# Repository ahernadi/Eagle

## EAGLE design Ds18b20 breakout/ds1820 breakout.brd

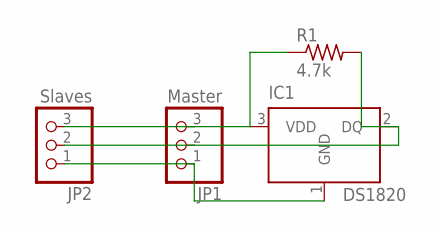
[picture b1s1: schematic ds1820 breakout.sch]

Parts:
IC1: DS1820; TO-92
JP1: Master; 1X03
JP2: Slaves; 1X03
R1: 4.7k; 0207/7

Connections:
GND: IC1.1 (GND), JP1.1, JP2.1
unnamed: IC1.2 (DQ), JP1.2, JP2.2, R1.2
VCC: IC1.3 (VDD), JP1.3, JP2.3, R1.1

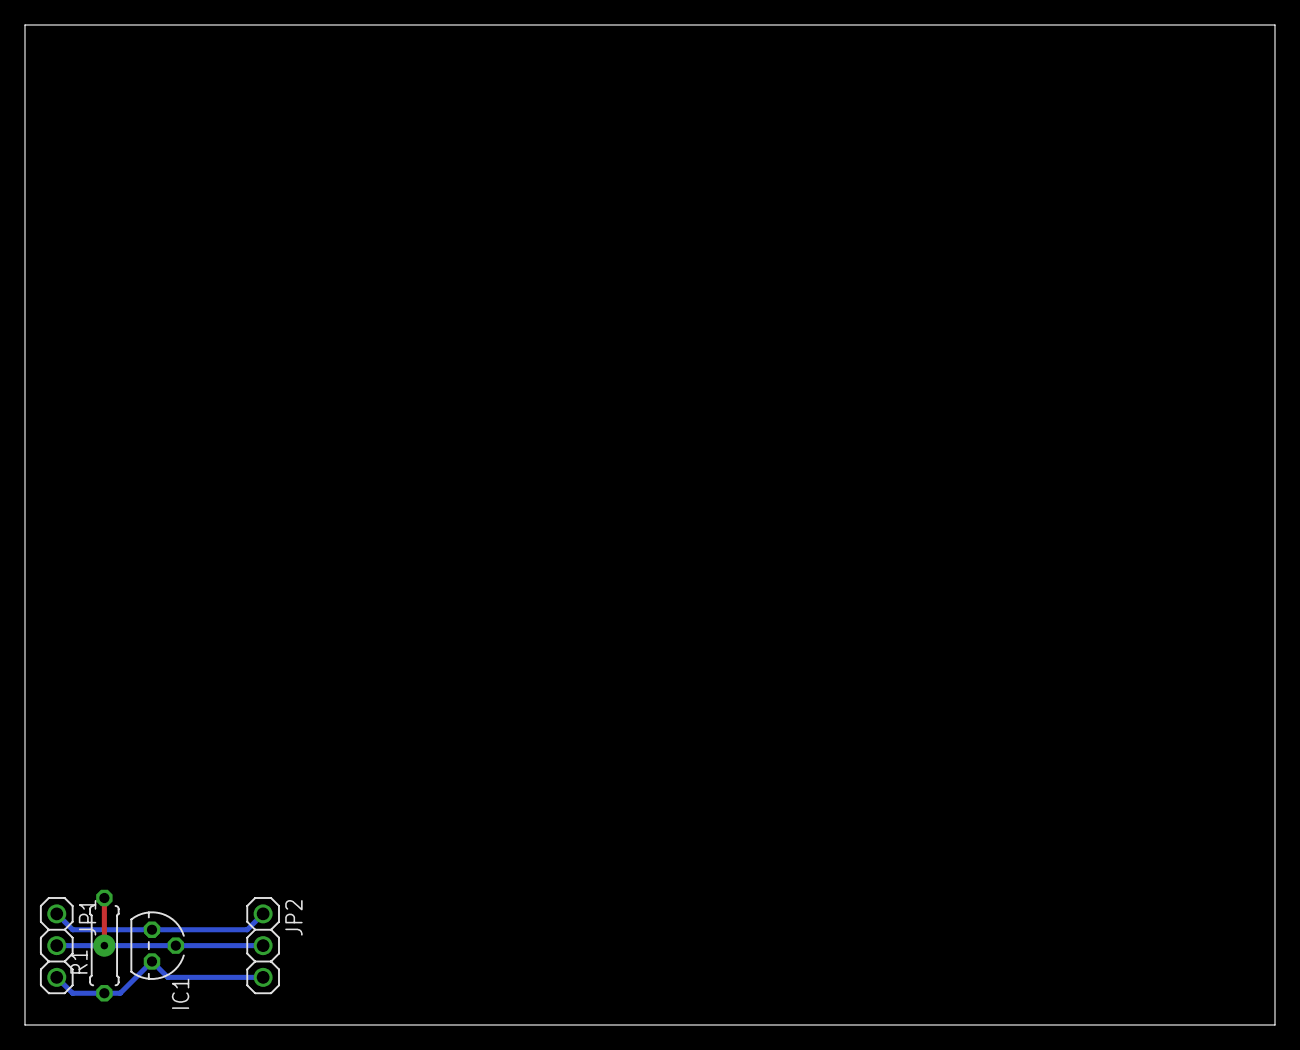
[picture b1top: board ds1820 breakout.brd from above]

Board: 2 copper layers, 100.0 x 80.0 mm, 4 parts (0 on the bottom side), 3 nets.

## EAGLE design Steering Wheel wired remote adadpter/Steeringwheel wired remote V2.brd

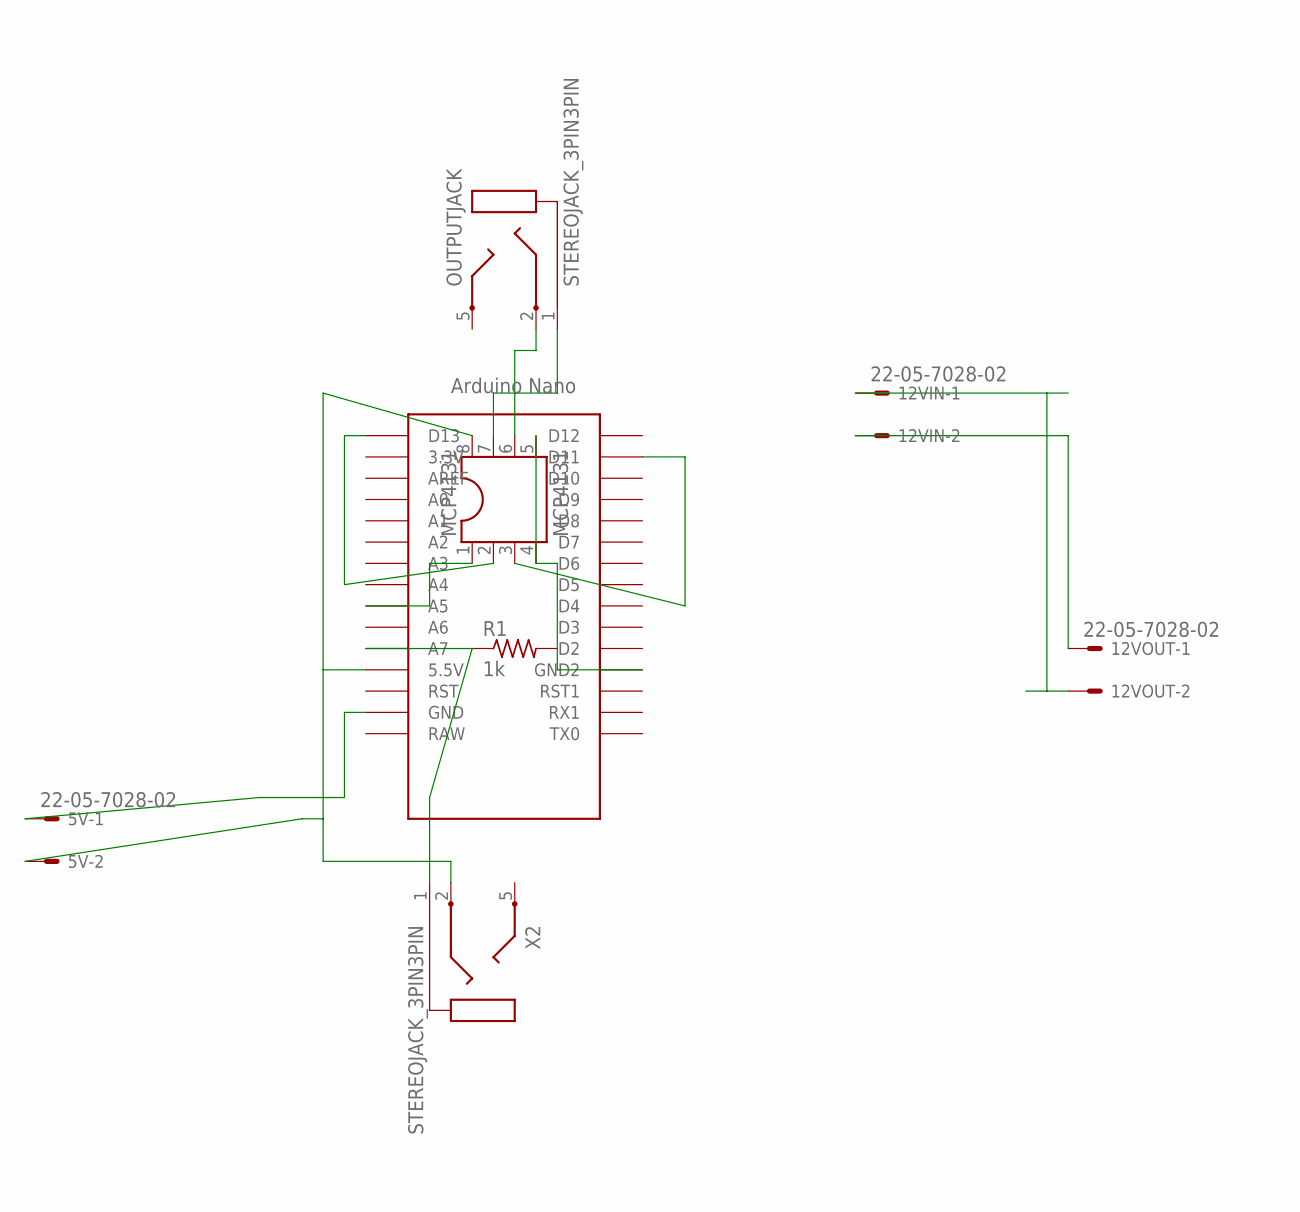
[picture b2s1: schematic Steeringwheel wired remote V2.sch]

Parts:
5V, 12VIN, 12VOUT: 22-05-7028-02; 7395-02
IC1: MCP4131; DIL08
OUTPUTJACK: STEREOJACK_3PIN3PIN; STX3000
R1: 1k; 0204/5
U$2: NANO; NANO_NOISPC
X2: STEREOJACK_3PIN3PIN; STX3000

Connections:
GND: 5V.1, IC1.4 (GND), IC1.5 (P0A), R1.2, U$2.GND, U$2.GND1 (GND2)
unnamed: IC1.3 (SDI), U$2.D11
unnamed: IC1.2 (SCK), U$2.D13
unnamed: R1.1, U$2.A7, X2.1
unnamed: IC1.6 (P0W), OUTPUTJACK.2
unnamed: 5V.2, IC1.8 (VCC), U$2.5V (5.5V), X2.2
unnamed: 12VIN.1, 12VOUT.2
unnamed: 12VIN.2, 12VOUT.1
unnamed: IC1.1 (!CS), U$2.A5
unnamed: IC1.7 (P0B), OUTPUTJACK.1

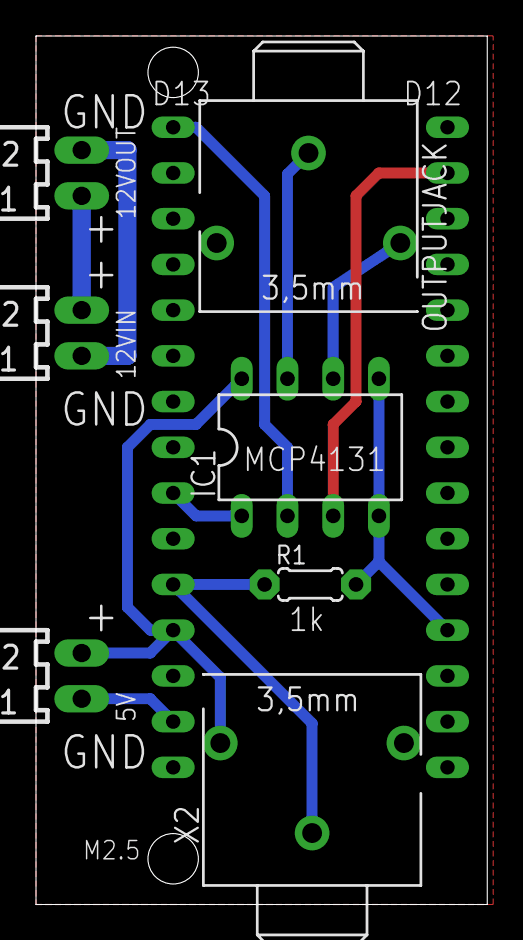
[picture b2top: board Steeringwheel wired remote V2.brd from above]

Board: 2 copper layers, 25.1 x 48.2 mm, 8 parts (0 on the bottom side), 10 nets.

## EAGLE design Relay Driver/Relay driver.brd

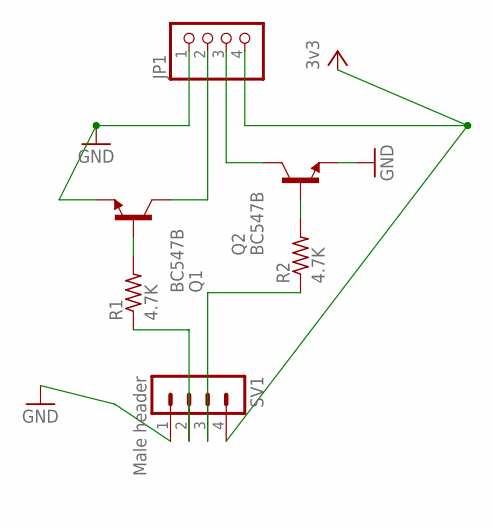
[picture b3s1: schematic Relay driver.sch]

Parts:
JP1: PINHD-1X4; 1X04
Q1, Q2: BC547B; TO92
R1, R2: 4.7K; 0204/5
SV1: Male header; MA04-1

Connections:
GND: JP1.1, Q1.1 (E), Q2.1 (E), SV1.1
unnamed: Q1.2 (B), R1.2
unnamed: Q2.2 (B), R2.2
unnamed: R1.1, SV1.2
unnamed: R2.1, SV1.3
unnamed: JP1.2, Q1.3 (C)
unnamed: JP1.3, Q2.3 (C)
VCC: JP1.4, SV1.4

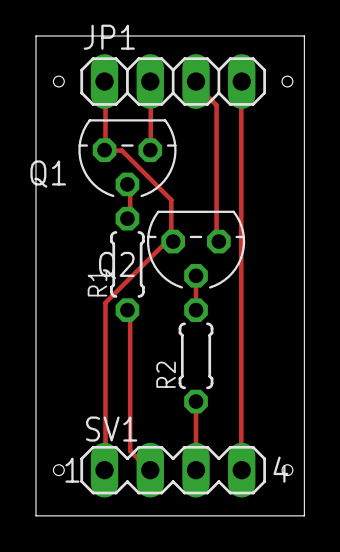
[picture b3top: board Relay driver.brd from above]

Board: 2 copper layers, 14.9 x 26.7 mm, 6 parts (0 on the bottom side), 8 nets.

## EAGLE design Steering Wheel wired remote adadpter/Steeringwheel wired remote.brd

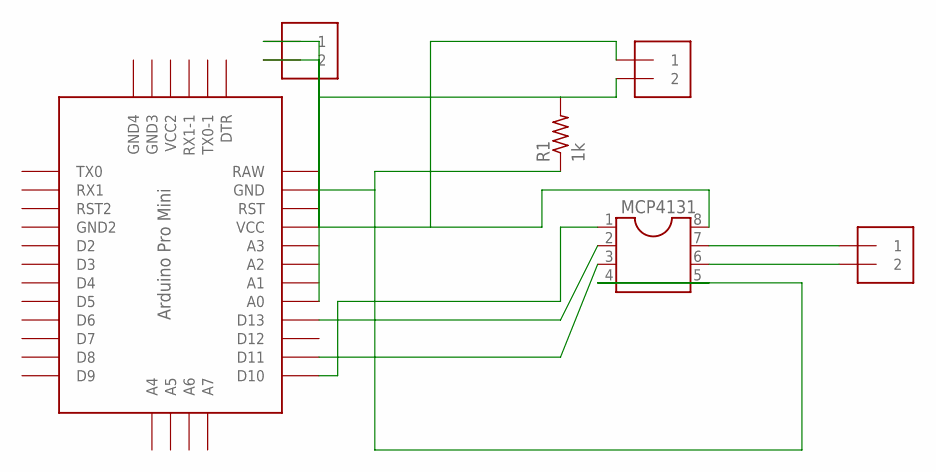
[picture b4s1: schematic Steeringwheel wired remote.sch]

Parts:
IC1: DIL8; DIL08
INPUT: 1X2-3.5MM
OUTPUT: 1X2-3.5MM
POWER: 1X2-3.5MM
R1: 1k; 0204/5
U$1: PRO-MINI

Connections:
unnamed: IC1.4 (GND), IC1.5 (P0A), POWER.1, R1.1, U$1.GND
unnamed: IC1.1 (!CS), U$1.D10
unnamed: IC1.2 (SCK), U$1.D13
unnamed: IC1.3 (SDI), U$1.D11
unnamed: IC1.8 (VCC), INPUT.1, POWER.2, U$1.VCC
unnamed: IC1.7 (P0B), OUTPUT.1
unnamed: IC1.6 (P0W), OUTPUT.2
unnamed: INPUT.2, R1.2, U$1.A0
RAW: U$1.RAW

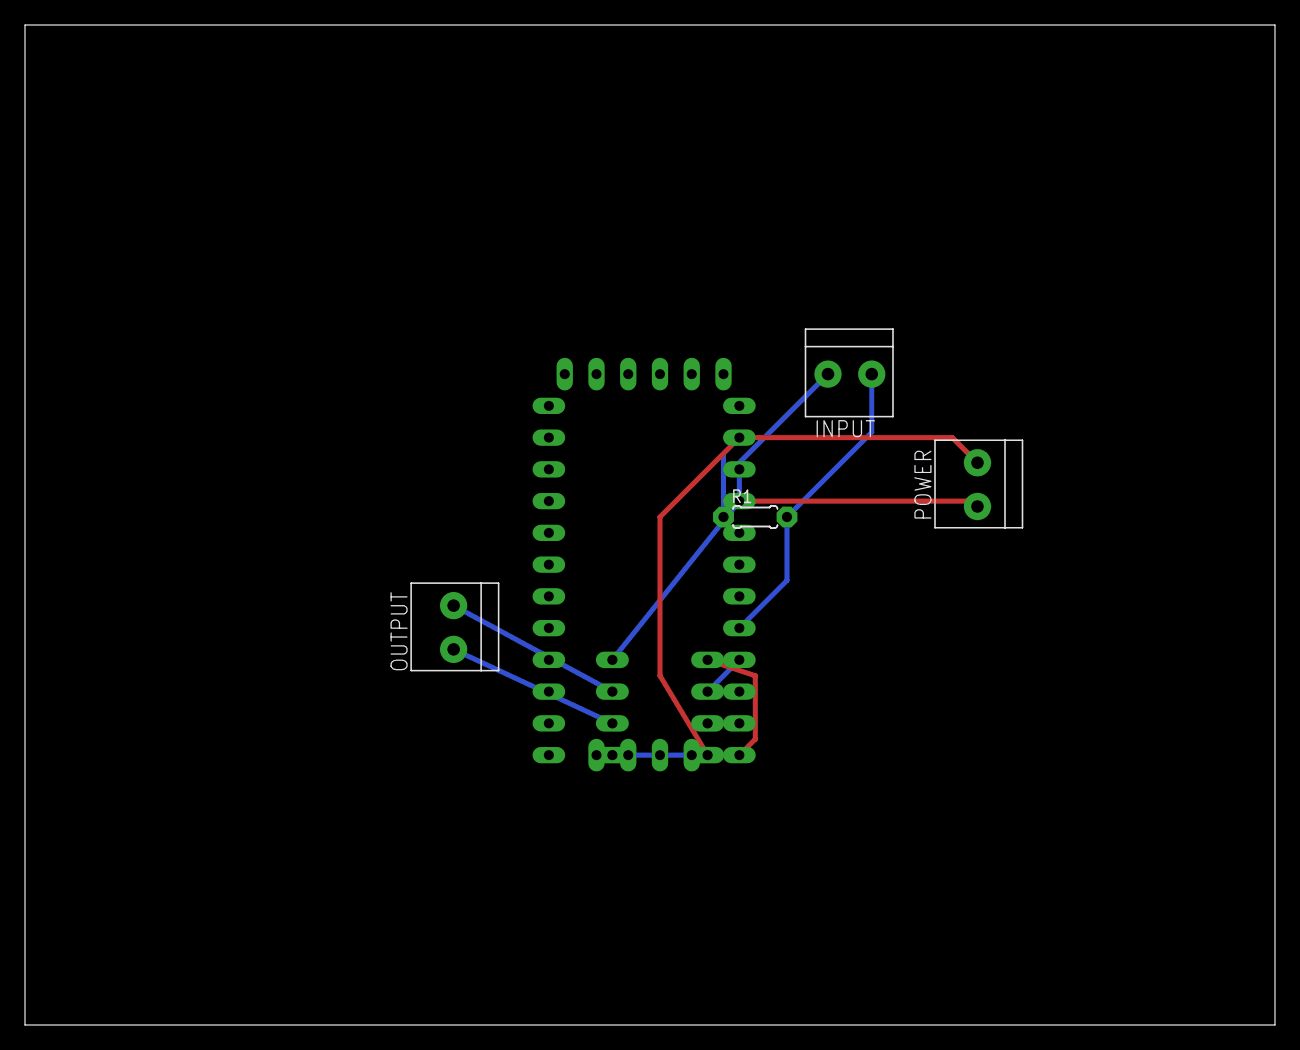
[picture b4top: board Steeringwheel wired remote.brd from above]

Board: 2 copper layers, 100.0 x 80.0 mm, 6 parts (1 on the bottom side), 8 nets.

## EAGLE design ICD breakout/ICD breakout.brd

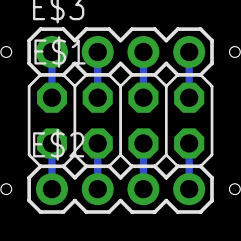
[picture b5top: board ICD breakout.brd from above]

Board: 2 copper layers, 3 parts (0 on the bottom side), 8 nets.

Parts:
E$1: 2X04
E$2, E$3: 1X04-BIG

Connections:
S$1: E$1.2, E$3.1
S$2: E$1.4, E$3.2
S$3: E$1.6, E$3.3
S$4: E$1.8, E$3.4
S$5: E$1.1, E$2.1
S$6: E$1.3, E$2.2
S$7: E$1.5, E$2.3
S$8: E$1.7, E$2.4

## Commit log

2016-09-19 frst commit
2016-09-24 3 pin jacks added
2016-09-25 GND copper poor and .024 traces
2016-09-26 mounting holes
2016-10-12 altered mounting hole size
2016-10-13 ds18b20 + irrigation hat
2016-10-13 work in progress
2016-10-21 wired up shift reg and button
2016-10-27 more work done
2016-11-02 RTC and ESP8266 header added
